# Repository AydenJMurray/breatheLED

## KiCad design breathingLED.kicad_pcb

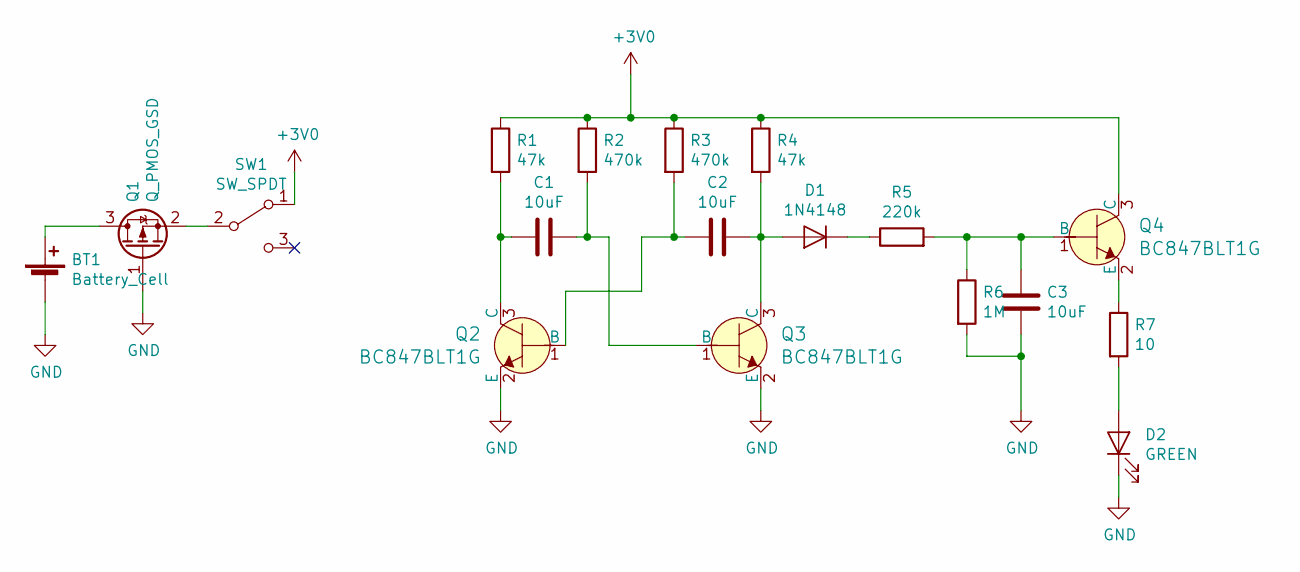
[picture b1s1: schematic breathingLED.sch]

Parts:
BT1: Battery_Cell; CoincellHolder
C1, C2, C3: 10uF; C_0805_2012Metric_Pad1.15x1.40mm_HandSolder
D1: 1N4148; D_SOD-123
D2: GREEN; LED_1206_3216Metric_Pad1.42x1.75mm_HandSolder
Q1: Q_PMOS_GSD; SOT-23_Handsoldering
Q2, Q3, Q4: BC847BLT1G; SOT-23_Handsoldering; MPN BC847BLT1G; Digi-Key_PN BC847BLT1GOSCT-ND
R1, R4: 47k; R_0805_2012Metric_Pad1.15x1.40mm_HandSolder
R2, R3: 470k; R_0805_2012Metric_Pad1.15x1.40mm_HandSolder
R5: 220k; R_0805_2012Metric_Pad1.15x1.40mm_HandSolder
R6: 1M; R_0805_2012Metric_Pad1.15x1.40mm_HandSolder
R7: 10; R_0805_2012Metric_Pad1.15x1.40mm_HandSolder
SW1: SW_SPDT; JS102011SCQN

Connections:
+3V0: Q4.3 (C), R1.1, R2.1, R3.1, R4.1, SW1.1 (A)
GND: BT1.2 (-), C3.1, D2.1 (K), Q1.1 (G), Q2.2 (E), Q3.2 (E), R6.2; also elsewhere on the board
unnamed: BT1.1 (+), Q1.3 (D)
unnamed: C1.1, Q3.1 (B), R2.2
unnamed: C1.2, Q2.3 (C), R1.2
unnamed: C2.1, Q2.1 (B), R3.2
unnamed: C2.2, D1.2 (A), Q3.3 (C), R4.2
unnamed: C3.2, Q4.1 (B), R5.2, R6.1
unnamed: D1.1 (K), R5.1
unnamed 9: D2.2 (A), R7.2; also elsewhere on the board
unnamed: Q1.2 (S), SW1.2 (B)
unnamed: Q4.2 (E), R7.1

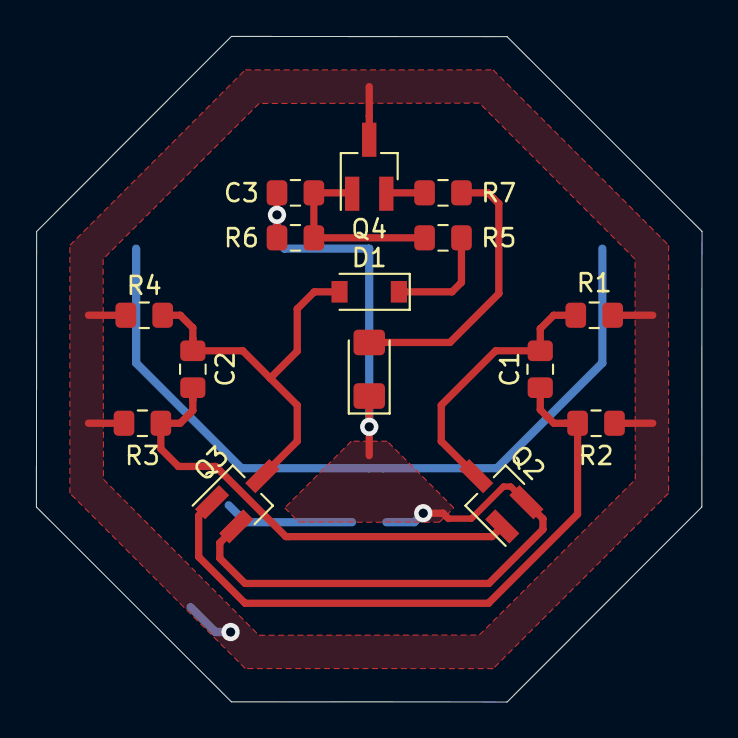
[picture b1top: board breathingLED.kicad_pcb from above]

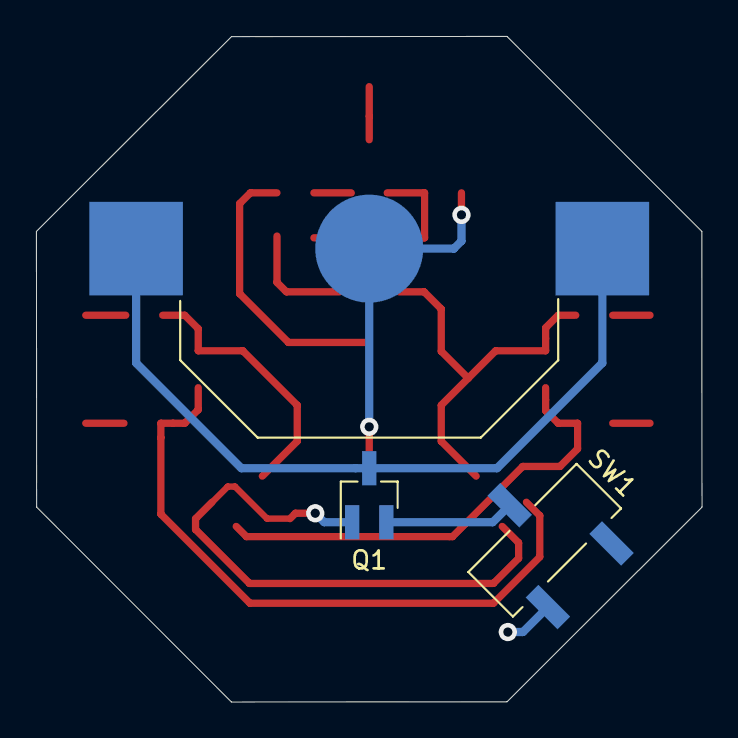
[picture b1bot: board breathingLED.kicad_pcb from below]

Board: 2 copper layers, 37.0 x 37.0 mm, 18 parts (3 on the bottom side), 12 nets.

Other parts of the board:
LED: GREEN; LED_1206_3216Metric_Pad1.42x1.75mm_HandSolder

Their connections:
GND: LED.1; also elsewhere on the board
unnamed 9: LED.2; also elsewhere on the board

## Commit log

2019-08-19 .gitignore
    Added Github Kicad.gitignore
2019-08-19 Routing complete
    Finished routing PCB with small copper plane near centre for ground
